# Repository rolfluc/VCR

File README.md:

# VCR
Voltage Controlled Resistor for use as an intermediate to convert voltage into a resistance.

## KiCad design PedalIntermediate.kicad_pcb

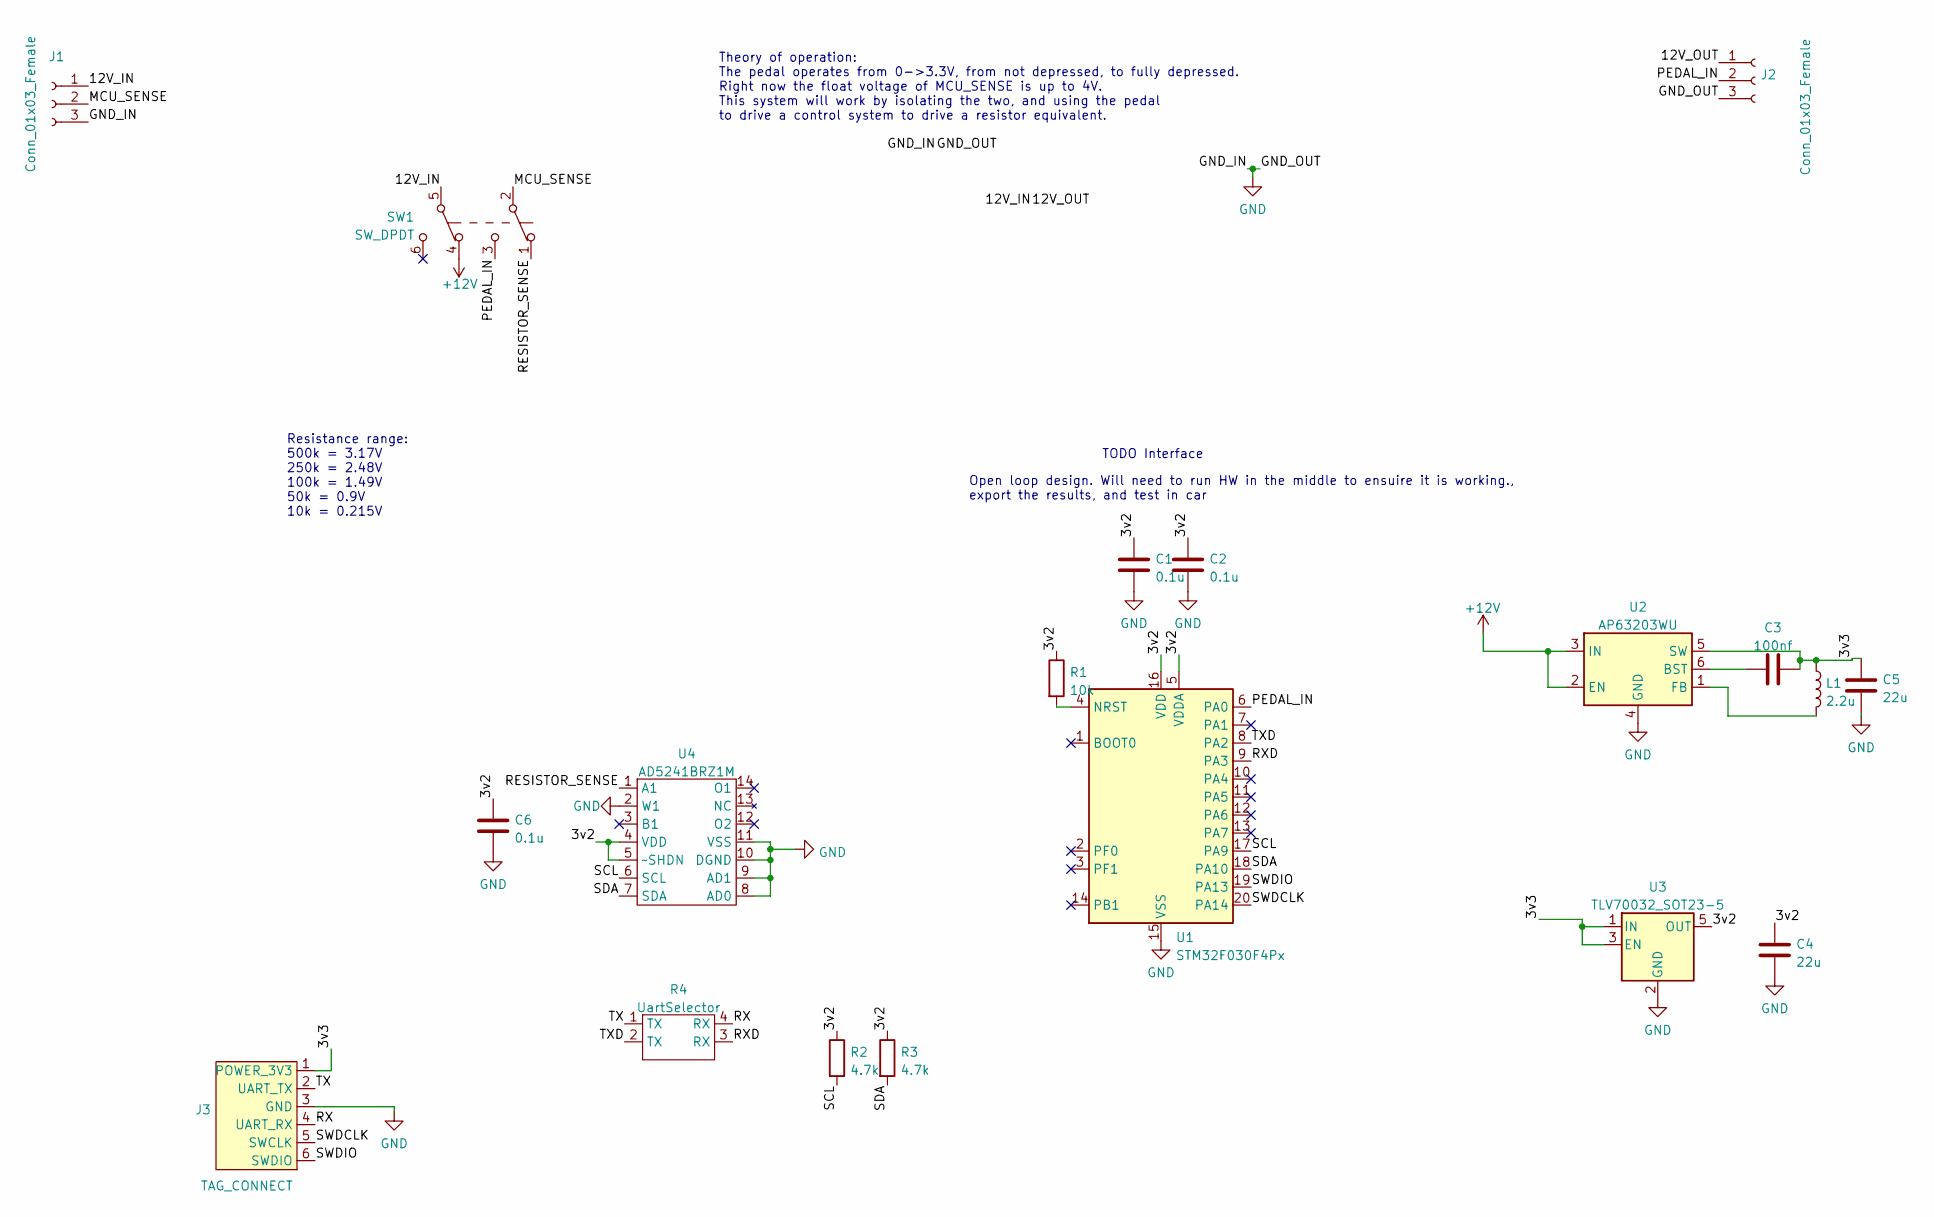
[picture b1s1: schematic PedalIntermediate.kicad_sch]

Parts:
C1, C2, C6: 0.1u; C_0402_1005Metric
C3: 100nf; C_0402_1005Metric
C4, C5: 22u; C_0402_1005Metric
J1, J2: Conn_01x03_Female; PinHeader_1x03_P2.54mm_Vertical
J3: TAG_CONNECT; Tag-Connect_TC2030-IDC-FP_2x03_P1.27mm_Vertical
L1: 2.2u; L_0603_1608Metric
R1: 10k; R_0402_1005Metric
R2, R3: 4.7k; R_0402_1005Metric
R4: UartSelector
SW1: SW_DPDT; SW_EG2208
U1: STM32F030F4Px; TSSOP-20_4.4x6.5mm_P0.65mm
U2: AP63203WU; TSOT-23-6
U3: TLV70032_SOT23-5; SOT-23-5
U4: AD5241BRZ1M; SOIC-14_3.9x8.7mm_P1.27mm

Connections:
+12V: SW1.4 (A), U2.2 (EN), U2.3 (IN)
/3v2: C1.1, C2.1, C4.1, C6.1, R1.1, R2.1, R3.1, U1.5 (VDDA), U1.16 (VDD), U3.5 (OUT), U4.4 (VDD), U4.5 (~SHDN)
/3v3: C3.2, C5.1, J3.1 (POWER_3V3), L1.1, U2.5 (SW), U3.1 (IN), U3.3 (EN)
/12V_IN: J1.1, J2.1, SW1.5 (B)
/MCU_SENSE: J1.2, SW1.2 (B)
/PEDAL_IN: J2.2, SW1.3 (C), U1.6 (PA0)
/RESISTOR_SENSE: SW1.1 (A), U4.1 (A1)
/RX: J3.4 (UART_RX), R4.4 (RX)
/RXD: R4.3 (RX), U1.9 (PA3)
/SCL: R2.2, U1.17 (PA9), U4.6 (SCL)
/SDA: R3.2, U1.18 (PA10), U4.7 (SDA)
/SWDCLK: J3.5 (SWCLK), U1.20 (PA14)
/SWDIO: J3.6 (SWDIO), U1.19 (PA13)
/TX: J3.2 (UART_TX), R4.1 (TX)
/TXD: R4.2 (TX), U1.8 (PA2)
GND: C1.2, C2.2, C4.2, C5.2, C6.2, J1.3, J2.3, J3.3 (GND), U1.15 (VSS), U2.4 (GND), U3.2 (GND), U4.2 (W1), U4.8 (AD0), U4.9 (AD1), U4.10 (DGND), U4.11 (VSS)
unnamed: C3.1, U2.6 (BST)
unnamed: L1.2, U2.1 (FB)
unnamed: R1.2, U1.4 (NRST)

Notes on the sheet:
Resistance range: 500k = 3.17V 250k = 2.48V 100k = 1.49V 50k = 0.9V 10k = 0.215V
Theory of operation: The pedal operates from 0->3.3V, from not depressed, to fully depressed. Right now the float voltage of MCU_SENSE is up to 4V. This system will work by isolating the two, and using the pedal to drive a control system to drive a resistor equivalent.
TODO Interface
Open loop design. Will need to run HW in the middle to ensuire it is working., export the results, and test in car

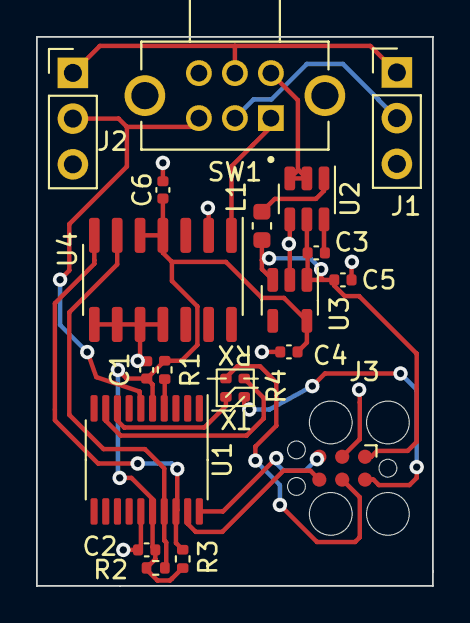
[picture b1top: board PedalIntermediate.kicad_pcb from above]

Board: 2 copper layers, 22.0 x 30.5 mm, 19 parts (0 on the bottom side), 19 nets.

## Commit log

2024-10-04 Working Pedal Interface
